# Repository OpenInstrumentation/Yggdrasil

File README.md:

# Yggdrasil
A sensing system for measuring rain through canopies.

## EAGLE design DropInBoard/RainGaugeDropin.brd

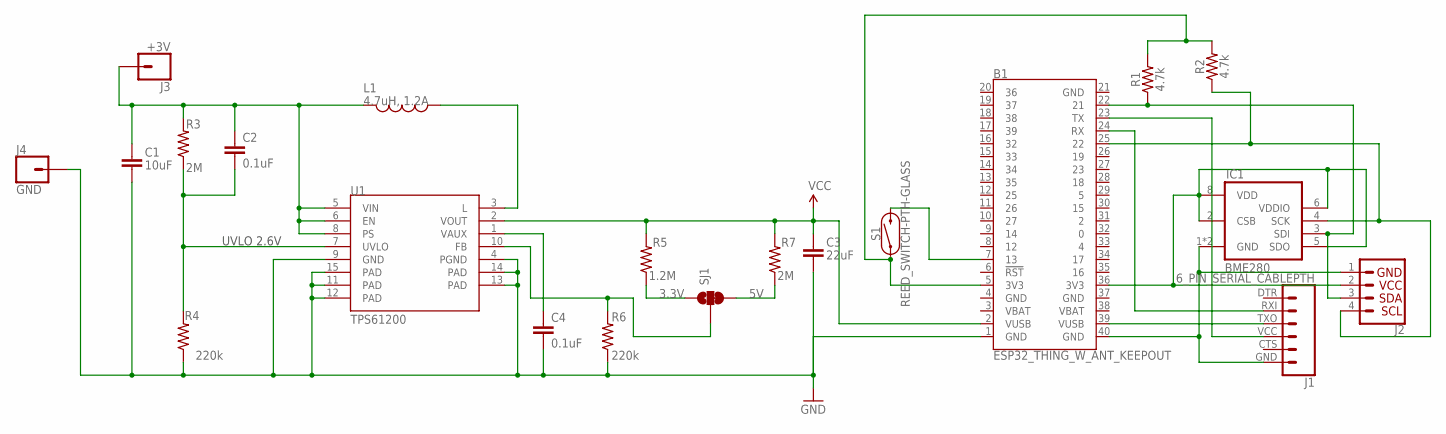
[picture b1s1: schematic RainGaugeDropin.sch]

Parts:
B1: ESP32_THING_W_ANT_KEEPOUT; ESP32_THING
C1: 10uF; 1206
C2, C4: 0.1uF; 0603-CAP
C3: 22uF; 0805
IC1: BME280
J1: 6_PIN_SERIAL_CABLEPTH; FTDI_BASIC
J2: QWIIC_CONNECTORJS-1MM; 1X04_1MM_RA
J3: +3V; 1X01_OFFSET
J4: GND; 1X01_OFFSET
L1: 4.7uH, 1.2A; CDRH2D09
R1, R2: 4.7k; 0603
R3, R7: 2M; 0603-RES
R4, R6: 220k; 0603-RES
R5: 1.2M; 0603-RES
S1: REED_SWITCH-PTH-GLASS; REED_SWITCH_GLASS
SJ1: SOLDERJUMPER_2WAYPASTE2&3; SJ_3_PASTE2&3
U1: TPS61200; QFN-10_PAD

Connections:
3.3V: R5.1, SJ1.1
5V: R7.1, SJ1.3
FB: R6.2, SJ1.2, U1.10 (FB)
GND: B1.1 (GND), C1.2, C3.2, C4.2, J4.1, R4.1, R6.1, U1.4 (PGND), U1.9 (GND), U1.11 (PAD), U1.12 (PAD), U1.13 (PAD), U1.14 (PAD), U1.15 (PAD)
unnamed: B1.40 (GND), IC1.1 (GND), IC1.7 (GND), J1.GND (6), J2.1 (GND)
unnamed: B1.36 (3V3), IC1.2 (CSB), IC1.5 (SDO), IC1.6 (VDDIO), IC1.8 (VDD), J2.2 (VCC)
unnamed: B1.25 (22), IC1.4 (SCK), J2.4 (SCL), R2.1
unnamed: L1.P$1 (1), U1.3 (L)
unnamed: B1.22 (21), IC1.3 (SDI), J2.3 (SDA), R1.1
unnamed: B1.39 (VUSB), J1.VCC (4)
unnamed: B1.7 (13), S1.P$2 (2)
unnamed: C4.1, U1.1 (VAUX)
unnamed: B1.23 (TX), J1.TXO (3)
unnamed: B1.5 (3V3), R1.2, R2.2, S1.P$1 (1)
unnamed: B1.24 (RX), J1.RXI (2)
UVLO: C2.2, R3.1, R4.2, U1.7 (UVLO)
VCC: B1.2 (VUSB), C3.1, R5.2, R7.2, U1.2 (VOUT)
VIN: C1.1, C2.1, J3.1, L1.P$2 (2), R3.2, U1.5 (VIN), U1.6 (EN), U1.8 (PS)

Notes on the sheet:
UVLO 2.6V

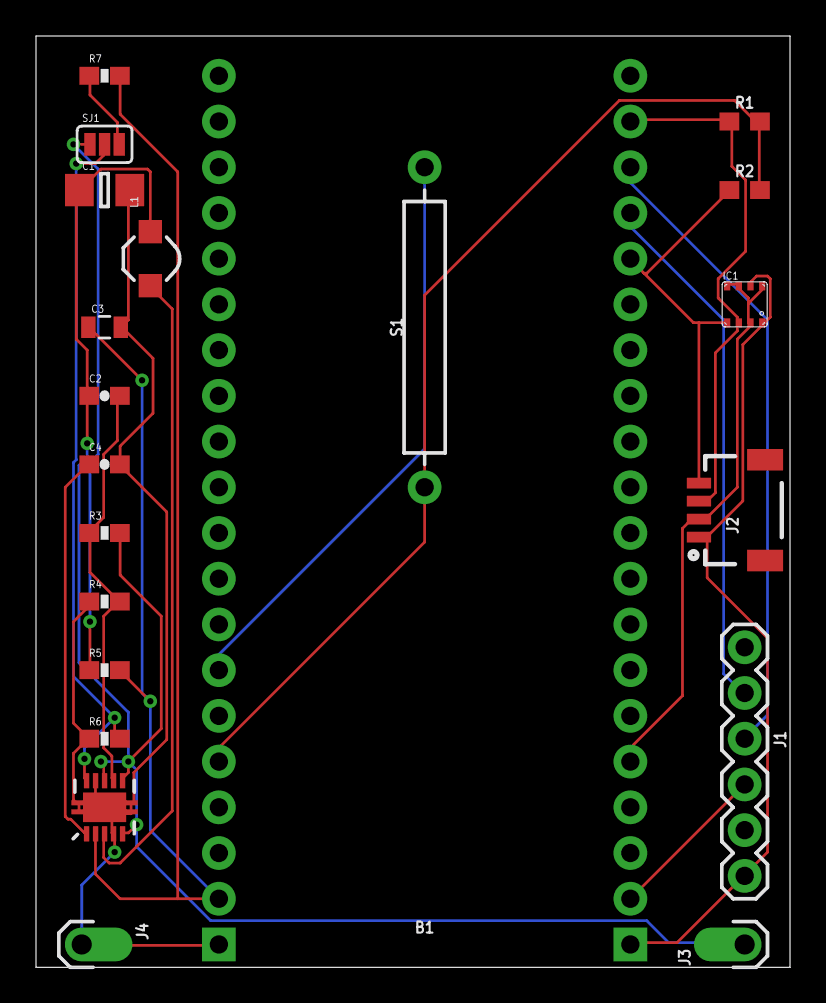
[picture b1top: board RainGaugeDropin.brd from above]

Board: 2 copper layers, 41.9 x 51.7 mm, 21 parts (0 on the bottom side), 18 nets.

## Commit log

2018-10-03 Added DropIn board files

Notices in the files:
parts and their libraries:
SparkFun-Boards: Licensing: Creative Commons ShareAlike 4.0 International - https://creativecommons.org/licenses/by-sa/4.0
